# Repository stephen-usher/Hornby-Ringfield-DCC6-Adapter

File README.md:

# Hornby-Ringfield-DCC6-Adapter
 
 This board is designed to interface a 6 pin DCC decoder with the Hornby ringfield motor found in most models from the mid-1970s until the late 1980s. With the appropriate wires and connectors it can be used as a substitute to the original wiring without the need to solder to any of the original parts of the model.
 
 In addition to the PCB you will need:
 >2x SOD-323 format diodes with at least 100mA throughput (for directional lights)
 >2x 2010 SMD 10 ohm resistors
 >2x 6 way 1.27mm pitch through-hole socket
 >Optional 0603 1uF SMD ceramic capacitor
 >Wires with connectors. The ones to connect to the motor block and unpowered bogie on diesels can be obtained from Peter's Spares. The 2.78mm spade connectors are more difficult to source.
 
 Although this was designed to be used with Hornby locos it will work with others, such as Lima. I've recently used this board to upgrade a Lima 08 shunter, just soldering wires, bridging the resistor pads (as the Lima motor has a higher resistance) and swapping the motor wires as the Lima motor runs in the opposite direction.
 
 The reason that the board has two 10 ohm resistors in parallel is that the Hornby ringfield motor has a resistance of 13 ohms. With the DCC decoder outputting 16V (pulsed) there is a possibility of the motor, if stalled, drawing more than the 1 amp which most 6 pin DCC decoders can handle. The parallel capacitors add an extra 5 ohms (spread between two resistors so as to reduce the current in any one resistor), taking the total to 18 ohms, with a maximum current at 16V less than one amp.
 
 The optional 1uF capacitor helps dampen any voltage spikes from the motor.

 The terminology used for the ends of the loco are based upon diesel locos with "forward" being the No.1 end and the rear the No.2 end. Hornby locos have the motor at the No.2 end. So, "Rail 1" connects to the front, undriven, bogie on a diesel and the loco with a tender driven steam loco and "Track 2" to the motor body.

 The DCC Decoder I use is the Bachmann E-Z Command 90 degree 6 Pin DCC Decoder (Ananlogue Compatible), 36-556RA. I've found that for Hornby motors CV10 (back-EMF cut-off) should be given the value 35 and CV212 (back-EMF strength) set to 128.
  
 Note: I've not yet tested the lighting but the circuit conforms to the specification given in the DCC Wiki.

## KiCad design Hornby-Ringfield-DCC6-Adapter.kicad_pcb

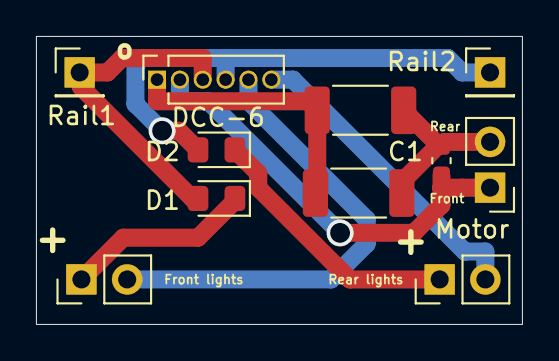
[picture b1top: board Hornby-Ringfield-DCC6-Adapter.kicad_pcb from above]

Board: 2 copper layers, 27.0 x 16.0 mm, 11 parts (0 on the bottom side), 9 nets.

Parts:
C1: 1uF; C_0603_1608Metric_Pad1.08x0.95mm_HandSolder
D1, D2: D; D_0805_2012Metric_Pad1.15x1.40mm_HandSolder
DCC-6: Conn_01x06_Female; PinSocket_1x06_P1.27mm_Vertical
Front lights: Conn_01x02_Male; PinHeader_1x02_P2.54mm_Vertical
MOTOR1_R1, MOTOR1_R2: 10; R_2010_5025Metric_Pad1.40x2.65mm_HandSolder
Motor: Conn_01x02_Male; PinHeader_1x02_P2.54mm_Vertical
Rail1, Rail2: Conn_01x01_Male; PinHeader_1x01_P2.54mm_Vertical
Rear lights: Conn_01x02_Male; PinHeader_1x02_P2.54mm_Vertical

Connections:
LED-NEG-1: DCC-6.5, Front lights.2
LED-NEG-2: DCC-6.6, Rear lights.2
LIGHT-PWR1: D1.1, Front lights.1
LIGHT-PWR2: D2.1, Rear lights.1
MOTOR1: DCC-6.1, MOTOR1_R1.1, MOTOR1_R2.1
MOTOR1_OUT: C1.1, MOTOR1_R1.2, MOTOR1_R2.2, Motor.2
MOTOR2: C1.2, DCC-6.2, Motor.1
RAIL1: D1.2, DCC-6.3, Rail1.1
RAIL2: D2.2, DCC-6.4, Rail2.1

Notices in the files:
Hornby-Ringfield-DCC6-Adapter.kicad_pcb:
Mk.2 © 2022 S.R.Usher
